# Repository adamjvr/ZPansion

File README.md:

# ZPansion
A Z stage control board for RepRap 3D Printers, designed to interface with mainboard expasnion pins.

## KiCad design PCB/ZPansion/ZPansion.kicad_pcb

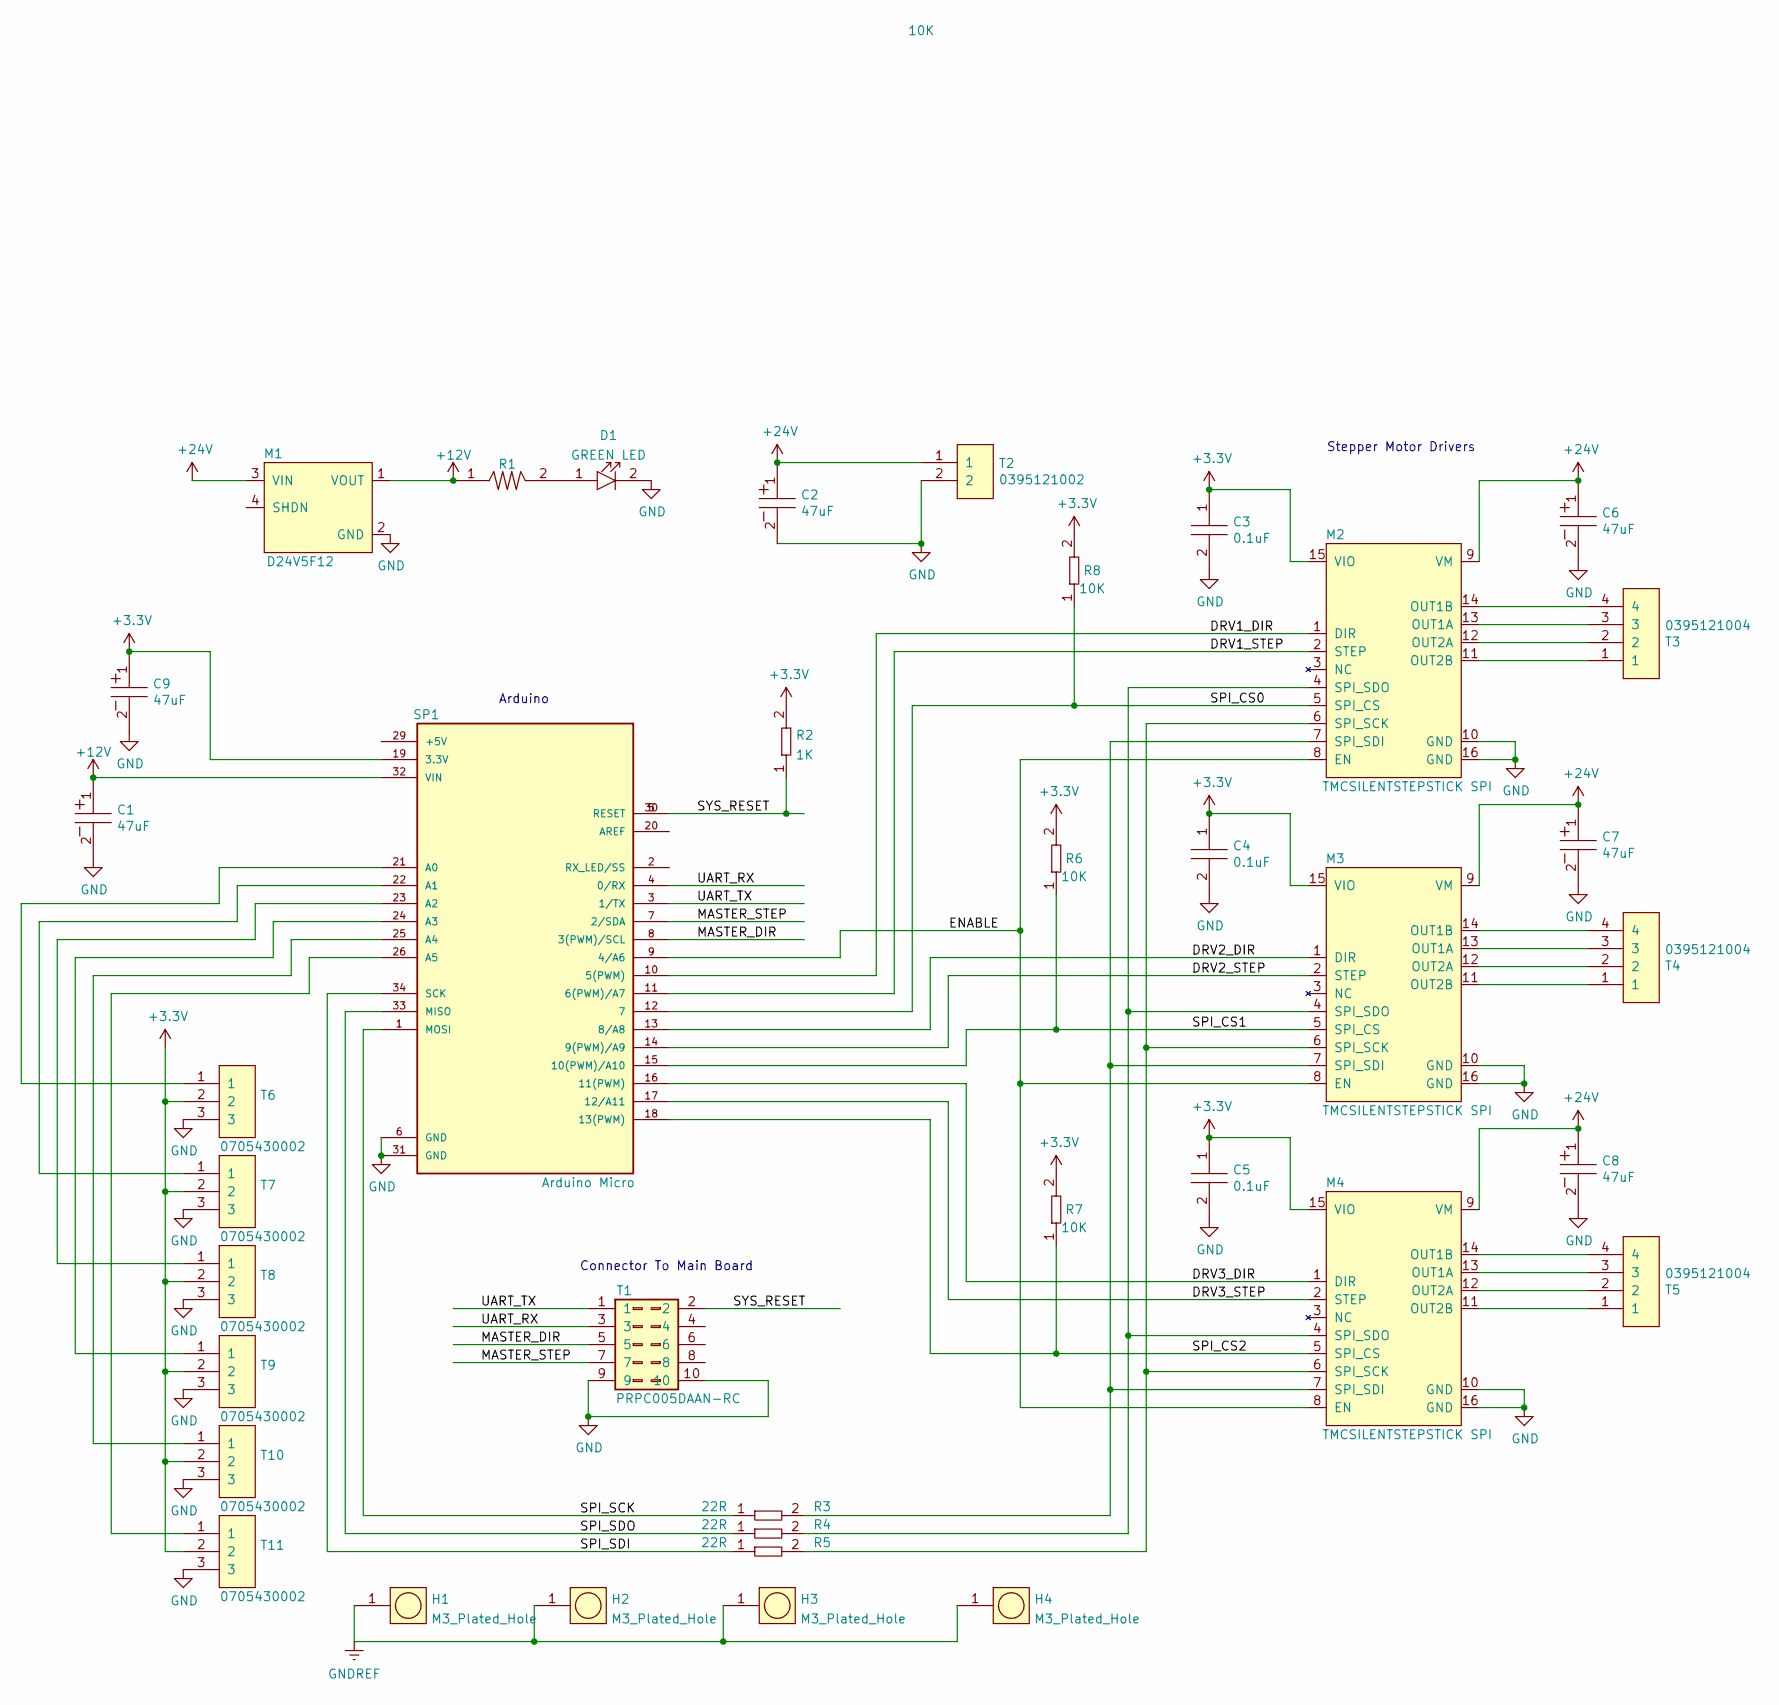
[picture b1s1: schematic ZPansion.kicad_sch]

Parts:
C1, C2, C6, C7, C8, C9: UCM1C470MCL1GS; Tolerance 20%; Voltage 16V; MFR# UCM1C470MCL1GS
C3, C4, C5: C0402C104K9PACTU; R0402; Tolerance 10%; Voltage 6.3V; MFR# C0402C104K9PACTU
D1: LTST-C194KGKT; LED0603; Tolerance *; Voltage 2.1V; MFR# LTST-C194KGKT
H1, H2, H3, H4: M3_Plated_Hole; M3_HOLE; Tolerance *; Voltage *; MFR# *
M1: D24V5F12; Tolerance *; Voltage 36VDC IN, 12VDC OUT; MFR# D24V5F12
M2, M3, M4: TMCSILENTSTEPSTICK; TMCSILENTSTEPSTICK_SPI; Tolerance N/A; Voltage 25V/5V; MFR# TMCSILENTSTEPSTICK SPI
R1: AT0603FRE0710KL; R0603; Tolerance 1%; Voltage *; MFR# AT0603FRE0710KL
R2: RC0402FR-071KL; R0402; Tolerance 1%; Voltage *; MFR# RC0402FR-071KL
R3, R4, R5: RC0402FR-0722RL; R0402; Tolerance 1%; Voltage *; MFR# RC0402FR-0722RL
R6, R7, R8: RC0402FR-0710KL; R0402; Tolerance 1%; Voltage *; MFR# RC0402FR-0710KL
SP1: Arduino_Micro; ARDUINO_A000053; Tolerance *; Voltage 3.3V/5V; MFR# A000053
T1: PRPC005DAAN-RC; PinHeader_2x05_P2.54mm_Vertical; Tolerance *; Voltage 250V; MFR# PRPC005DAAN-RC
T2: 0395121002; Tolerance *; Voltage 300V; MFR# 0395121002
T3, T4, T5: 0395121004; Tolerance *; Voltage 300V; MFR# 0395121004
T6, T7, T8, T9, T10, T11: 0705430002; Shrouded_Pin_Header_Straight_1x03_Pitch2.54mm; Tolerance *; Voltage 250V; MFR# 0705430002

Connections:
+3V3: C3.1, C4.1, C5.1, C9.1, M2.15 (VIO), M3.15 (VIO), M4.15 (VIO), R2.2, R6.2, R7.2, R8.2, SP1.19 (3.3V), T6.2, T7.2, T8.2, T9.2, T10.2, T11.2
+12V: C1.1, M1.1 (VOUT), R1.1, SP1.32 (VIN)
+24V: C2.1, C6.1, C7.1, C8.1, M1.3 (VIN), M2.9 (VM), M3.9 (VM), M4.9 (VM), T2.1
/DRV1_DIR: M2.1 (DIR), SP1.10 (5(PWM))
/DRV1_STEP: M2.2 (STEP), SP1.11 (6(PWM)/A7)
/DRV2_DIR: M3.1 (DIR), SP1.13 (8/A8)
/DRV2_STEP: M3.2 (STEP), SP1.14 (9(PWM)/A9)
/DRV3_DIR: M4.1 (DIR), SP1.16 (11(PWM))
/DRV3_STEP: M4.2 (STEP), SP1.17 (12/A11)
/ENABLE: M2.8 (EN), M3.8 (EN), M4.8 (EN), SP1.9 (4/A6)
/MASTER_DIR: SP1.8 (3(PWM)/SCL), T1.5
/MASTER_STEP: SP1.7 (2/SDA), T1.7
/SPI_CS0: M2.5 (SPI_CS), R8.1, SP1.12 (7)
/SPI_CS1: M3.5 (SPI_CS), R6.1, SP1.15 (10(PWM)/A10)
/SPI_CS2: M4.5 (SPI_CS), R7.1, SP1.18 (13(PWM))
/SPI_SCK: R3.1, SP1.1 (MOSI)
/SPI_SDI: R5.1, SP1.34 (SCK)
/SPI_SDO: R4.1, SP1.33 (MISO)
/SYS_RESET: R2.1, SP1.5 (RESET), SP1.30 (RESET), T1.2
/UART_RX: SP1.4 (0/RX), T1.3
/UART_TX: SP1.3 (1/TX), T1.1
GND: C1.2, C2.2, C3.2, C4.2, C5.2, C6.2, C7.2, C8.2, C9.2, D1.2, M1.2 (GND), M2.10 (GND), M2.16 (GND), M3.10 (GND), M3.16 (GND), M4.10 (GND), M4.16 (GND), SP1.6 (GND), SP1.31 (GND), T1.9, T1.10, T2.2, T6.3, T7.3, T8.3, T9.3, T10.3, T11.3
GNDREF: H1.1, H2.1, H3.1, H4.1
unnamed: D1.1, R1.2
unnamed: M2.4 (SPI_SDO), M3.4 (SPI_SDO), M4.4 (SPI_SDO), R4.2
unnamed: M2.6 (SPI_SCK), M3.6 (SPI_SCK), M4.6 (SPI_SCK), R5.2
unnamed: M2.7 (SPI_SDI), M3.7 (SPI_SDI), M4.7 (SPI_SDI), R3.2
unnamed: M2.11 (OUT2B), T3.1
unnamed: M2.12 (OUT2A), T3.2
unnamed: M2.13 (OUT1A), T3.3
unnamed: M2.14 (OUT1B), T3.4
unnamed: M3.11 (OUT2B), T4.1
unnamed: M3.12 (OUT2A), T4.2
unnamed: M3.13 (OUT1A), T4.3
unnamed: M3.14 (OUT1B), T4.4
unnamed: M4.11 (OUT2B), T5.1
unnamed: M4.12 (OUT2A), T5.2
unnamed: M4.13 (OUT1A), T5.3
unnamed: M4.14 (OUT1B), T5.4
unnamed: SP1.21 (A0), T6.1
unnamed: SP1.22 (A1), T7.1
unnamed: SP1.23 (A2), T8.1
unnamed: SP1.24 (A3), T9.1
unnamed: SP1.25 (A4), T10.1
unnamed: SP1.26 (A5), T11.1

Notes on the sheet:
Connector To Main Board
Arduino
Stepper Motor Drivers

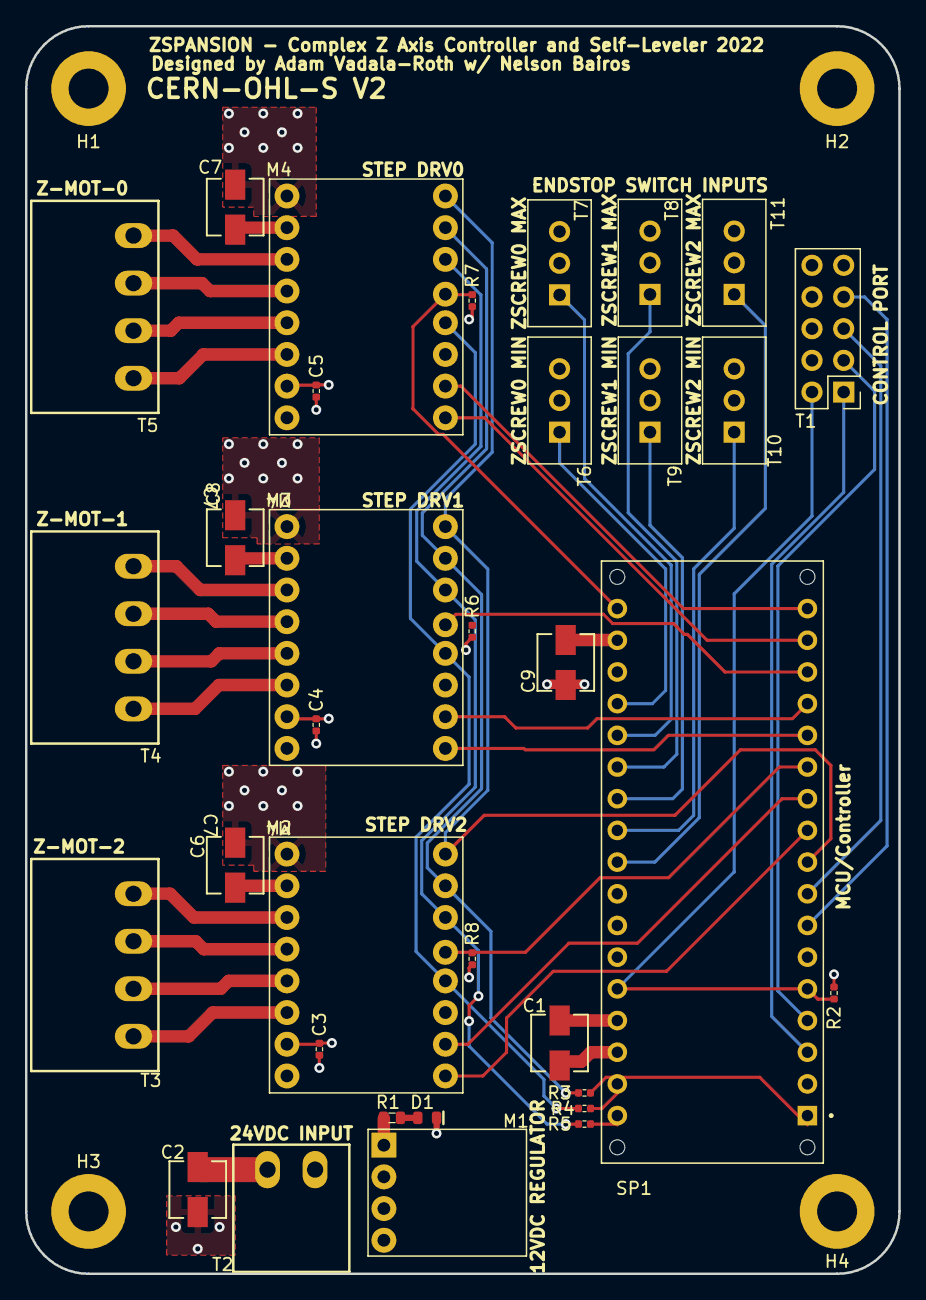
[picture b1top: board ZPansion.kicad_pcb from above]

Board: 4 copper layers, 70.0 x 100.0 mm, 38 parts (0 on the bottom side), 45 nets.

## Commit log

2021-12-07 Schematic
    Most of the first pass to schematic finished, need to figure out what the VIN max of the Arduino micro is and either get a regulator or tie it to 24V, going to check the mA out of the Arduino Micro 3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
2022-01-02 Schematic Finished PCB Placed
    Finished scheamtic, added regulator for 12V and started PCB. Placed all parts and got 3D models for most working.
2022-01-15 PCB Done
    Finished PCB design and route. Schematic tweaked along the way, termination resistors added to SPI just in case.

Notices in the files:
PCB/ZPansion/ZPansion.kicad_pcb:
CERN-OHL-S V2
parts and their libraries:
Copyright 2016 Accelerated Designs. All rights reserved.
